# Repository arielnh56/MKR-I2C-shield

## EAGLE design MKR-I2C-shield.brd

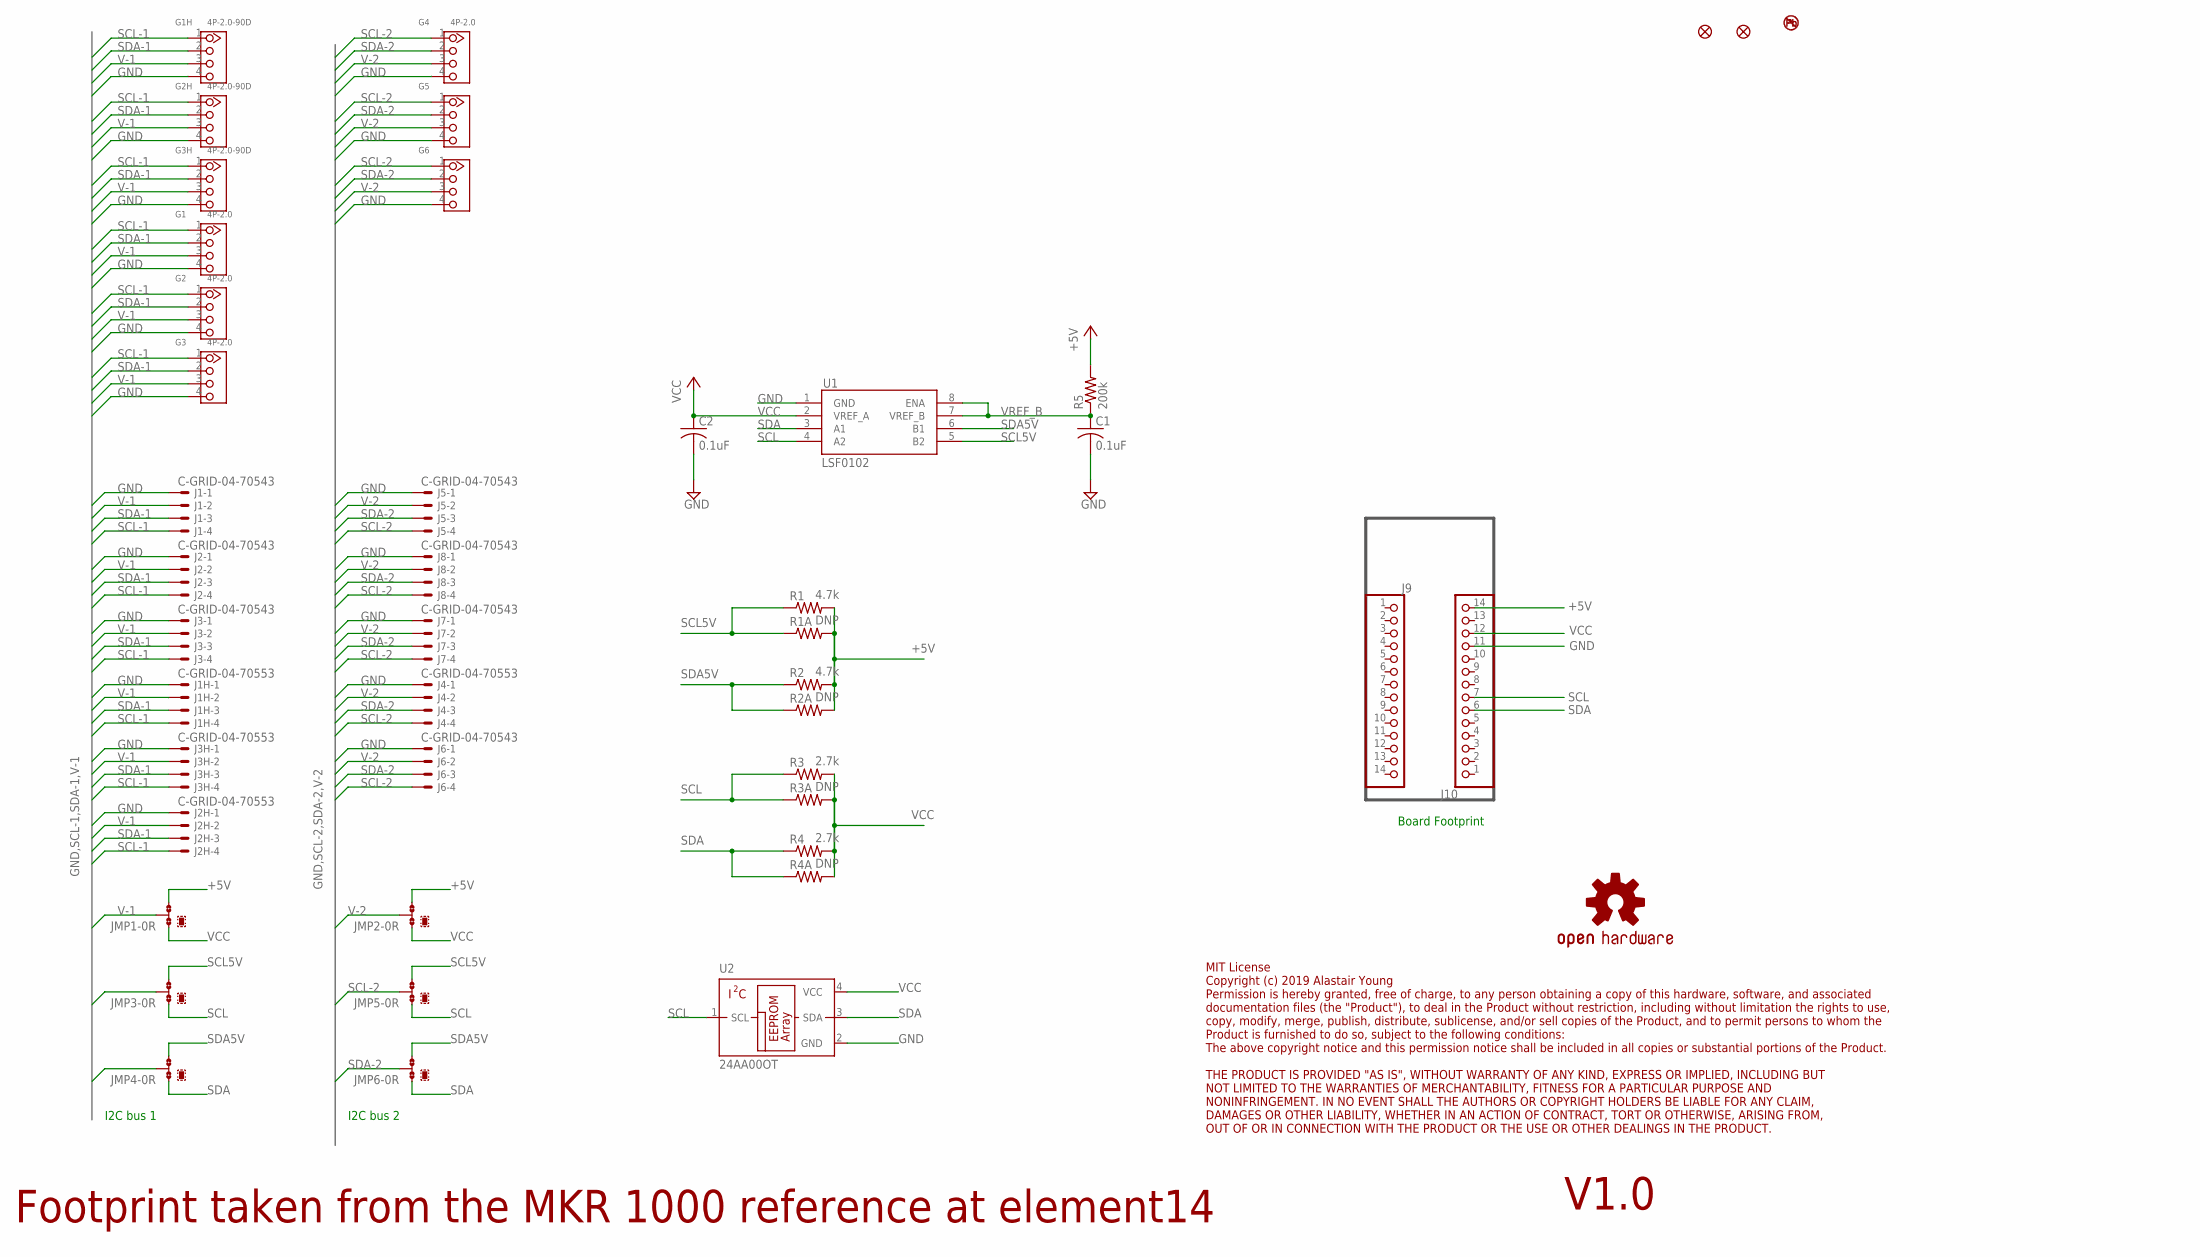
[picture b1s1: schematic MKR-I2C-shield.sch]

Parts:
C1, C2: 0.1uF; C0603
FD1, FD2: FIDUCIAL1X2; FIDUCIAL-1X2
G1, G2, G3, G4, G5, G6: 4P-2.0; HW4-2.0
G1H, G2H, G3H: 4P-2.0-90D; HW4-2.0-90D
J1, J2, J3, J5, J6, J7, J8: C-GRID-04-70543; 70543-04
J1H, J2H, J3H, J4: C-GRID-04-70553; 70553-04
J9, J10: DNP; 1X14
JMP1, JMP2, JMP3, JMP4, JMP5, JMP6: 0R-JUMPB; B0R-JMP
LOGO1: OSHW-LOGOL; OSHW-LOGO-L
LOGO2: NO_PB_LOGO; NO_PB_LOGO_0.120
R1, R2: 4.7k; R0603
R1A, R2A, R3A, R4A: DNP; 0204/5
R3, R4: 2.7k; R0603
R5: 200k; R0603
U1: LSF0102; DCT_R-PDSO-G8
U2: 24AA00OT; SOT23-5L

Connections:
+5V: J10.14, JMP1.3, JMP2.3, R1.2, R1A.2, R2.2, R2A.2, R5.2
GND: C1.2, C2.2, G1.4, G1H.4, G2.4, G2H.4, G3.4, G3H.4, G4.4, G5.4, G6.4, J1.1, J1H.1, J2.1, J2H.1, J3.1, J3H.1, J4.1, J5.1, J6.1, J7.1, J8.1, J10.11, U1.1 (GND), U2.2 (GND)
SCL: J10.7, JMP3.1, JMP5.1, R3.1, R3A.1, U1.4 (A2), U2.1 (SCL)
SCL5V: JMP3.3, JMP5.3, R1.1, R1A.1, U1.5 (B2)
SCL-1: G1.1, G1H.1, G2.1, G2H.1, G3.1, G3H.1, J1.4, J1H.4, J2.4, J2H.4, J3.4, J3H.4, JMP3.2
SCL-2: G4.1, G5.1, G6.1, J4.4, J5.4, J6.4, J7.4, J8.4, JMP5.2
SDA: J10.6, JMP4.1, JMP6.1, R4.1, R4A.1, U1.3 (A1), U2.3 (SDA)
SDA5V: JMP4.3, JMP6.3, R2.1, R2A.1, U1.6 (B1)
SDA-1: G1.2, G1H.2, G2.2, G2H.2, G3.2, G3H.2, J1.3, J1H.3, J2.3, J2H.3, J3.3, J3H.3, JMP4.2
SDA-2: G4.2, G5.2, G6.2, J4.3, J5.3, J6.3, J7.3, J8.3, JMP6.2
V-1: G1.3, G1H.3, G2.3, G2H.3, G3.3, G3H.3, J1.2, J1H.2, J2.2, J2H.2, J3.2, J3H.2, JMP1.2
V-2: G4.3, G5.3, G6.3, J4.2, J5.2, J6.2, J7.2, J8.2, JMP2.2
VCC: C2.1, J10.12, JMP1.1, JMP2.1, R3.2, R3A.2, R4.2, R4A.2, U1.2 (VREF_A), U2.4 (VCC)
VREF_B: C1.1, R5.1, U1.7 (VREF_B), U1.8 (ENA)

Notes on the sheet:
Footprint taken from the MKR 1000 reference at element14
Board Footprint
I2C bus 1
I2C bus 2
MIT License Copyright (c) 2019 Alastair Young Permission is hereby granted, free of charge, to any person obtaining a copy of this hardware, software, and associated documentation files (the "Product"), to deal in the Product without restriction, including without limitation the rights to use, copy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
V1.0

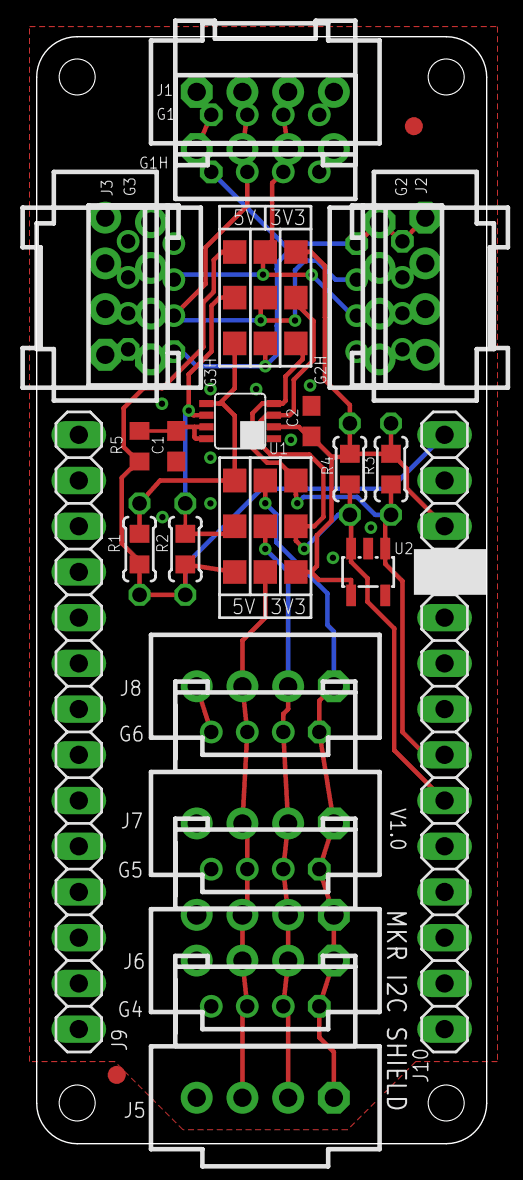
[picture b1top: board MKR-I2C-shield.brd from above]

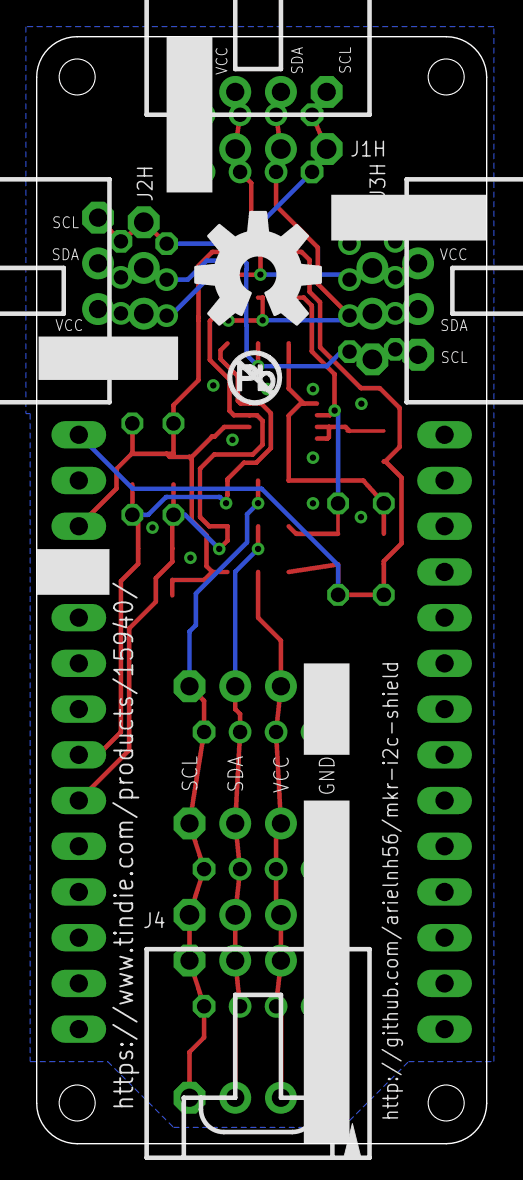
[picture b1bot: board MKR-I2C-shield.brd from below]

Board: 2 copper layers, 25.0 x 61.5 mm, 45 parts (6 on the bottom side), 14 nets.

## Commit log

2019-01-18 v0.1
    initial 0.1 proto to oshpark
2019-02-04 v1.0
    first production run

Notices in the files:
parts and their libraries:
SparkFun-Aesthetics: Licensing: Creative Commons ShareAlike 4.0 International - https://creativecommons.org/licenses/by-sa/4.0
